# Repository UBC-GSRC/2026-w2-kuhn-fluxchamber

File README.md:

# Flux Chamber Data Logger Firmware

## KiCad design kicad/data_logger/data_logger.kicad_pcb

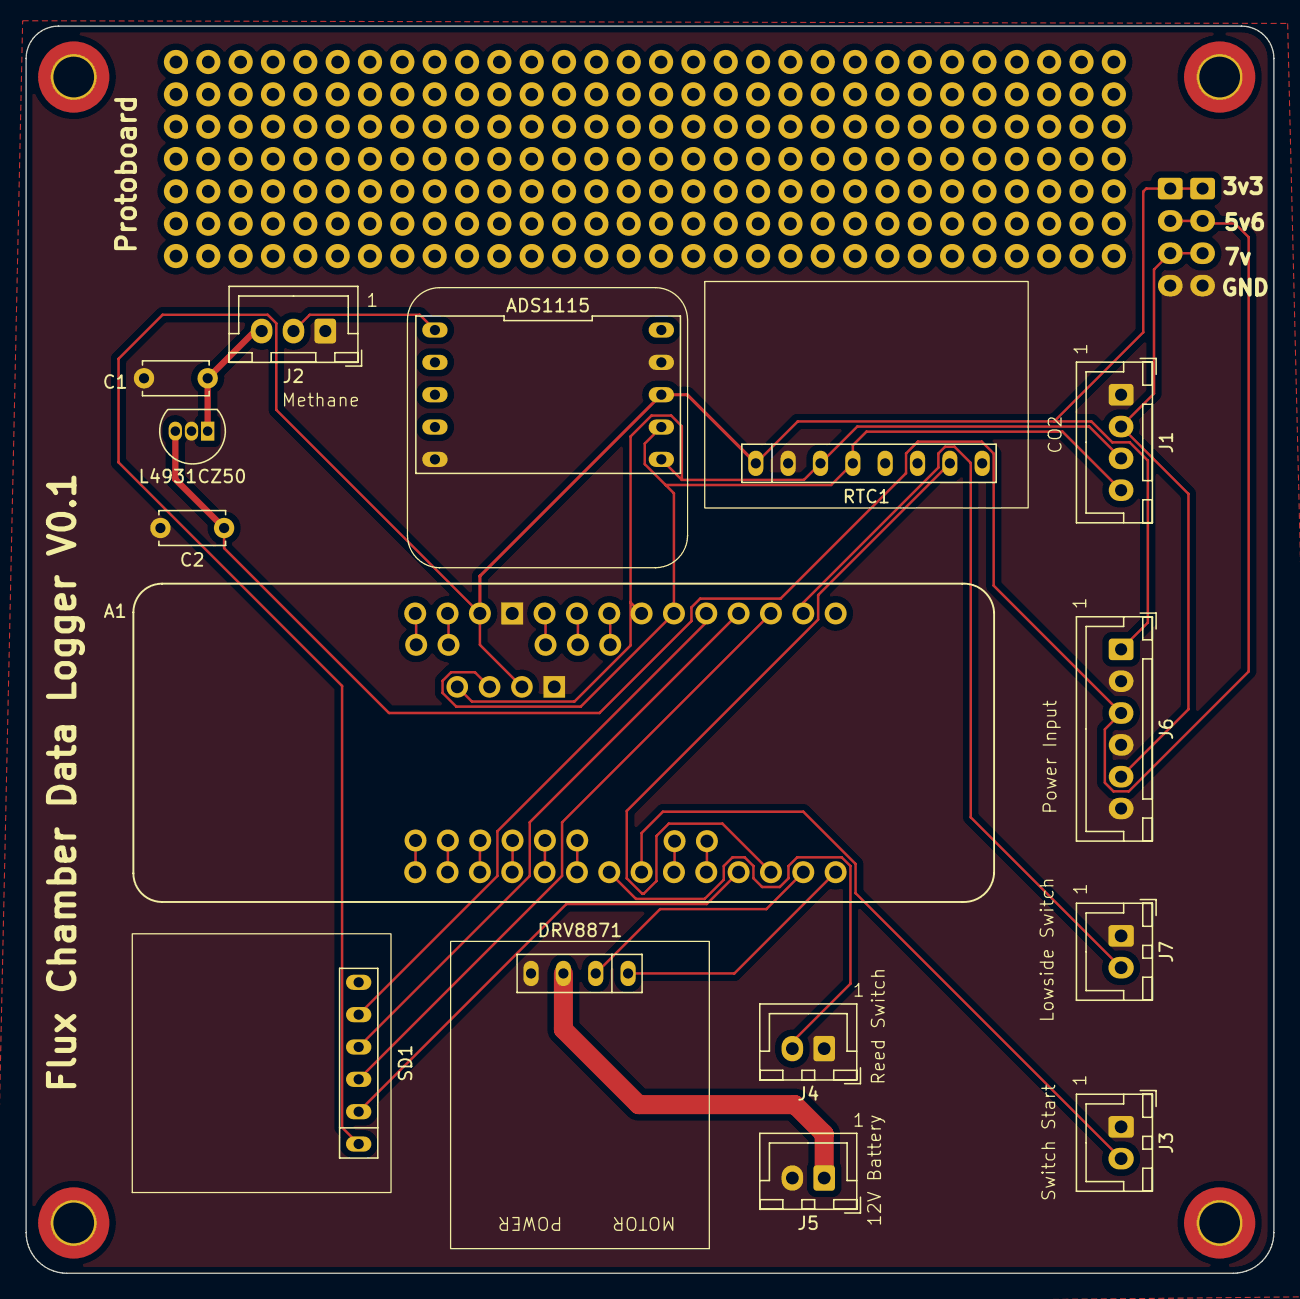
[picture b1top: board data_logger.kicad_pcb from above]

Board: 2 copper layers, 98.0 x 98.0 mm, 15 parts (0 on the bottom side), 19 nets.

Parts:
A1: Arduino_MKR_WAN_1310_Socket; Arduino_MKR_FOX_1200_Socket
ADS1115: ADS1115_breakout_soldered
C1, C2: 2.2uF; C_Disc_D5.0mm_W2.5mm_P5.00mm
DRV8871: DRV8871
J1: Conn_01x04_Pin; JST_XH_B4B-XH-A_1x04_P2.50mm_Vertical
J2: Conn_01x03_Pin; JST_XH_B3B-XH-A_1x03_P2.50mm_Vertical
J3, J4, J5, J7: Conn_01x02_Pin; JST_XH_B2B-XH-A_1x02_P2.50mm_Vertical
J6: Conn_01x06_Pin; JST_XH_B6B-XH-A_1x06_P2.50mm_Vertical
L4931CZ50: TO-92L_Inline
RTC1: RTC_DS3231_breakout
SD1: SD Breakout Board; SD_Breakout_offbrand

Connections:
+5V: C1.1, J2.3, L4931CZ50.1 (V_OUT)
/3V3: A1.3V3 (3.3V), ADS1115.8 (VCC), J6.1, RTC1.1 (Vin), SD1.1 (3V3)
/5V6: C2.1, J6.3, L4931CZ50.3 (V_IN)
/6to9V: J1.2, J6.5
/D2: A1.D2, SD1.2 (CS)
/D3: A1.D3, RTC1.7 (SQW)
/D7: A1.D7, J7.2
/MISO: A1.D10 (D10_MISO), SD1.5 (MISO/POCI)
/MOSI: A1.D8 (D8_MOSI), SD1.3 (MOSI/PICO)
/PWM_forward: A1.D4, DRV8871.2 (IN1)
/PWM_reverse: A1.D5, DRV8871.1 (IN2)
/SCK: A1.D9 (D9_SCK), SD1.4 (CLK)
/SCL: A1.D12 (D12/SCL), ADS1115.6 (SCL), J1.3, RTC1.3 (SCL)
/SDA: A1.D11 (D11/SDA), ADS1115.7 (SDA), J1.4, RTC1.4 (SDA)
/SW_Start: A1.A6, J3.2
/SW_manual: A1.A5, J4.2
/V_bat: DRV8871.3 (VM), J5.1
/methane_out: ADS1115.1 (A0), J2.2
GND1: A1.GND, ADS1115.5 (GND), ADS1115.9 (GND), C1.2, C2.2, DRV8871.4 (GND), J1.1, J2.1, J3.1, J4.1, J5.2, J6.2, J6.4, J6.6, J7.1, L4931CZ50.2 (GND), RTC1.2 (GND)

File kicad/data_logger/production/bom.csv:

Designator,Footprint,Quantity,Value,LCSC Part #
"_21, _20, _19, _18, _17, _16, _15, _14, _13, _12, _11, _10, _9, _8, _7, _6, _5, _4, _3, _2, ",,21,,
A1,Arduino_MKR_FOX_1200_Socket,1,Arduino_MKR_WAN_1310_Socket,
ADS1115,ADS1115_breakout_soldered,1,~,
"C1, C2",C_Disc_D5.0mm_W2.5mm_P5.00mm,2,2.2uF,
DRV8871,DRV8871,1,~,
J1,JST_XH_B4B-XH-A_1x04_P2.50mm_Vertical,1,Conn_01x04_Pin,
J2,JST_XH_B3B-XH-A_1x03_P2.50mm_Vertical,1,Conn_01x03_Pin,
"J3, J4, J5, J7",JST_XH_B2B-XH-A_1x02_P2.50mm_Vertical,4,Conn_01x02_Pin,
J6,JST_XH_B6B-XH-A_1x06_P2.50mm_Vertical,1,Conn_01x06_Pin,
L4931CZ50,TO-92L_Inline,1,~,
RTC1,RTC_DS3231_breakout,1,~,
SD1,SD_Breakout_offbrand,1,SD Breakout Board,

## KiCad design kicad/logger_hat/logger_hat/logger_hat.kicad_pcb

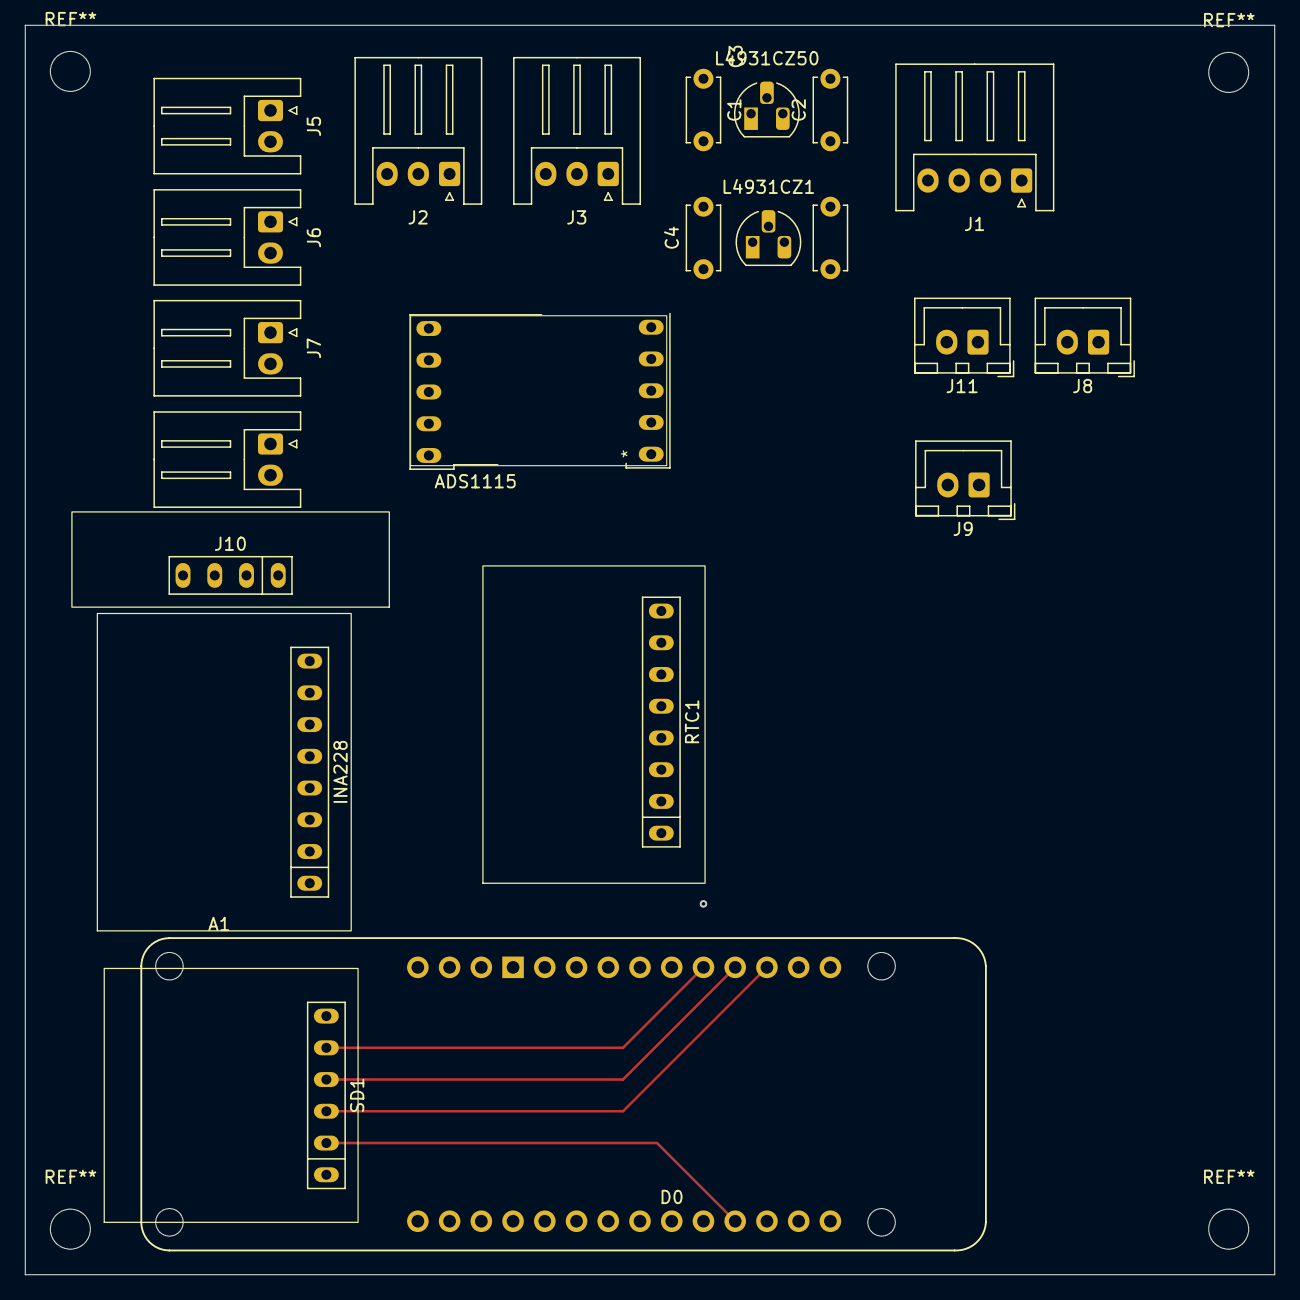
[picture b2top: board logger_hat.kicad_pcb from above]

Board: 2 copper layers, 100.0 x 100.0 mm, 22 parts (0 on the bottom side), 20 nets.

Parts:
A1: Arduino_MKR_WAN_1310_Socket; Arduino_MKR_FOX_1200_Socket
ADS1115: ADC_16-bit_ADS1115_breakout
C1, C4: 2.2uF; C_Disc_D5.0mm_W2.5mm_P5.00mm
C2, C3: 0.1uF; C_Disc_D5.0mm_W2.5mm_P5.00mm
INA228: INA228_adafruit_module
J1: CO2_sensor_conn; JST_XH_S4B-XH-A_1x04_P2.50mm_Horizontal
J2: 3V3_sensor_conn; JST_XH_S3B-XH-A_1x03_P2.50mm_Horizontal
J3: CH4_Sensor_conn; JST_XH_S3B-XH-A_1x03_P2.50mm_Horizontal
J4: SW_RD; JST_XH_S2B-XH-A_1x02_P2.50mm_Horizontal
J5: PWM_output_1; JST_XH_S2B-XH-A_1x02_P2.50mm_Horizontal
J6: SW_LOG; JST_XH_S2B-XH-A_1x02_P2.50mm_Horizontal
J7: PWM_output_2; JST_XH_S2B-XH-A_1x02_P2.50mm_Horizontal
J8: 7V_IN; JST_XH_B2B-XH-A_1x02_P2.50mm_Vertical
J9: 3V3_IN; JST_XH_B2B-XH-A_1x02_P2.50mm_Vertical
J10: Conn_01x04_Pin; SparkFun_Stemma_Adapter
J11: 5V6_IN; JST_XH_B2B-XH-A_1x02_P2.50mm_Vertical
L4931CZ1, L4931CZ50: TO-92_HandSolder
RTC1: RTC_DS3231_breakout
SD1: SD Breakout Board; SD_Breakout_offbrand

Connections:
+3V3: C4.1, J2.1, L4931CZ1.1 (V_OUT)
+5V: C1.1, J3.1, L4931CZ50.1 (V_OUT)
/3V3: A1.3V3 (3.3V), ADS1115.8 (VCC), INA228.1 (VIN), J9.1, J10.2, RTC1.1 (Vin), SD1.1 (3V3)
/5V6: C2.1, C3.1, J11.1, L4931CZ1.3 (V_IN), L4931CZ50.3 (V_IN)
/6to9V: J1.2, J8.1
/D2: A1.D2, SD1.2 (CS)
/D3: A1.D3, RTC1.7 (SQW)
/D4: A1.D4, J6.1
/D5: A1.D5, J4.1
/D7: A1.D7, J7.1
/MISO: A1.D10 (D10_MISO), SD1.5 (MISO/POCI)
/MOSI: A1.D8 (D8_MOSI), SD1.3 (MOSI/PICO)
/PWM: A1.D1, J5.1
/SCK: A1.D9 (D9_SCK), SD1.4 (CLK)
/SCL: A1.D12 (D12/SCL), ADS1115.6 (SCL), INA228.3 (SCL), J1.4, J10.4, RTC1.3 (SCL)
/SDA: A1.D11 (D11/SDA), ADS1115.7 (SDA), INA228.4 (SDA), J1.3, J10.3, RTC1.4 (SDA)
/V_bat: INA228.5 (VBUS), INA228.7 (VIN+)
/methane_out: ADS1115.1 (A0), J3.2
/sensor_out: ADS1115.2 (A1), J2.2
GND: A1.GND, ADS1115.5 (GND), ADS1115.9 (GND), C1.2, C2.2, C3.2, C4.2, INA228.2 (GND), J1.1, J2.3, J3.3, J4.2, J5.2, J6.2, J7.2, J8.2, J9.2, J10.1, J11.2, L4931CZ1.2 (GND), L4931CZ50.2 (GND), RTC1.2 (GND), SD1.6 (GND)

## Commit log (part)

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2026-01-05 Moving progress from other repo to this one
    Copy and pasted the work from flux_chamber_data_logger that is hosted on my account. But we're moving away from using personal accounts to host repos.
2026-01-05 Bill of Materials
    Added Bill of Materials to flux chamber repository
2026-01-05 updated title
    Updated bill of materials to bill_of_materials for readability
2026-01-06 Rearranging
2026-01-07 Adding work in progress kicad schematic
2026-01-07 Adding UML state machine diagram of what the data logger firmware needs to do
2026-01-07 Removing spaces in folder names
2026-01-08 Transitioning to a statemachine. Having some oddities with sleeping and Serial communication.
2026-01-09 Adding notes
    adding a notes section including inspiration, key components,
    project summary, updates, and more
2026-01-12 Adding datasheets and new schematic for methane sensor
2026-01-12 Made markdown files
2026-01-13 Adding voltage reading from methane sensor connected to ADS1115
2026-01-19 Adding lowside switch driver to main
2026-01-22 Changing data to be stored in struct
2026-01-24 Adding serial command infrastructure to set the time while the physical switch on the controller is set to 'calibration' mode.
2026-01-24 Updating schematics as I resolder things to the prototype
2026-01-27 Some LoRa testing and updating logs
2026-01-30 Adding INA228 chip to schematics and cleaning things up a bit
2026-01-30 Adding reed switch input example. Just makes an led blink for now but will need to be low power wakeup
2026-01-30 Work log
2026-02-07 Making more changes. Thinking of still using the connectors to deliver various power levels
2026-02-07 Read work log
2026-02-10 Changing delays to be non-blocking millis()
2026-02-10 Updating work log
2026-04-23 Schematic changes to add motor driver and routed traces
2026-04-28 Committing before testing new PCB V0.1
2026-04-30 Updating sd card writing test
2026-04-30 Adding vent opening and closing
2026-04-30 Switching pins for direction
2026-04-30 Initial energy budget script
2026-05-01 Adding new serial commands list and changing flow diagram
2026-05-01 Adding comments for serial commands
2026-06-01 Updating UML png
2026-06-08 Doing more serial port testing. Setting and getting time works. Only concerned about reading continuous but haven't tested yet.
2026-06-10 Updating the serial commands so that there is a terminal menu that allows you to control the functions of the chamber via microusb connection.
2026-06-15 Adding LoRa transmit as an option for serial command. Mostly for testing
2026-06-17 Forgot to check if inputs were functional with external interrupts when I rearranged pins... Shouldve taken better notes!
